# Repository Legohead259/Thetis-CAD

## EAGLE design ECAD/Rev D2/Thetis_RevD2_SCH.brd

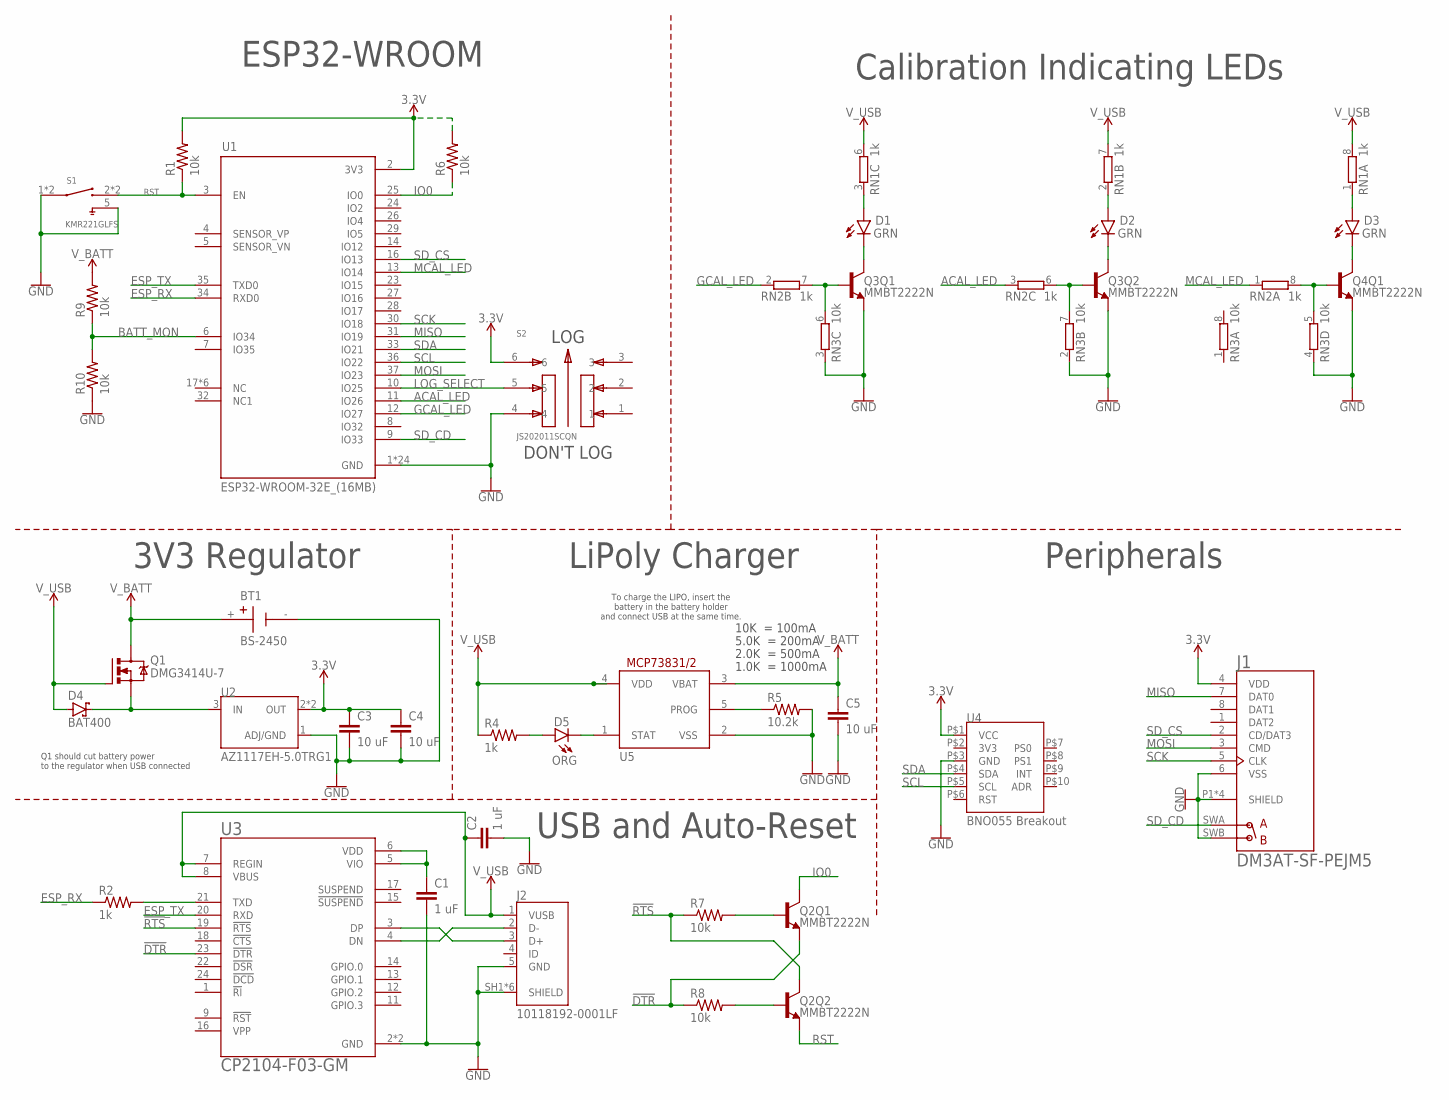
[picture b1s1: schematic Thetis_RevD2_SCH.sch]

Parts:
BT1: BS-2450; BAT_BS-2450
C1, C2: 1 uF; C0603
C3, C4, C5: 10 uF; C0603
D1, D2, D3: GRN; LEDC1608X65N
D4: BAT400; SOT23
D5: ORG; LEDC1608X65N
J1: DM3AT-SF-PEJM5; HRS_DM3AT-SF-PEJM5
J2: 10118192-0001LF; AMPHENOL_10118192-0001LF
Q1: DMG3414U-7; SOT23
Q2, Q3, Q4: MMBT2222N; SC70-6
R1, R6, R7, R8, R9, R10: 10k; R0603
R2, R4: 1k; R0603
R5: 10.2k; R0603
RN1, RN2: 1k; EXB28V
RN3: 10k; EXB28V
S1: KMR221GLFS; SW_KMR221GLFS
S2: JS202011SCQN; SW_JS202011SCQN
U1: ESP32-WROOM-32E_(16MB); MODULE_ESP32-WROOM-32E_(16MB)
U2: AZ1117EH-5.0TRG1; SOT230P700X180-4N
U3: CP2104-F03-GM; QFN50P400X400X80-25N
U4: BNO055 Breakout; ADAFRUIT-BNO055-BREAKOUT-SMD
U5: MCP73831/OT; SOT23-5L

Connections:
3.3V: C3.1, C4.1, J1.4 (VDD), R1.2, R6.2, S2.6, U1.2 (3V3), U2.2 (OUT), U2.4 (OUT), U4.P$1 (VCC)
3V3: U4.P$2 (3V3)
!DTR: Q2.4 (E), R8.1, U3.23 (!DTR)
!RTS: Q2.6 (C), R7.1, U3.19 (!RTS)
ACAL_LED: RN2.3 (1), U1.11 (IO26)
BATT_MON: R9.1, R10.2, U1.6 (IO34)
ESP_RX: R2.1, U1.34 (RXD0)
ESP_TX: U1.35 (TXD0), U3.20 (RXD)
GCAL_LED: RN2.2 (1), U1.12 (IO27)
GND: BT1.-, C1.2, C2.2, C3.2, C4.2, C5.2, J1.6 (VSS), J1.P1 (SHIELD), J1.P2 (SHIELD), J1.P3 (SHIELD), J1.P4 (SHIELD), J1.SWB (B), J2.5 (GND), J2.SH1 (SHIELD), J2.SH2 (SHIELD), J2.SH3 (SHIELD), J2.SH4 (SHIELD), J2.SH5 (SHIELD), J2.SH6 (SHIELD), Q3.1 (E), Q3.4 (E), Q4.4 (E), R5.2, R10.1, RN3.2 (1), RN3.3 (1), RN3.4 (1), S1.1, S1.4 (1), S1.5, S2.4, U1.1 (GND), U1.15 (GND), U1.38 (GND), U1.39_1 (GND), U1.39_2 (GND), U1.39_3 (GND), U1.39_4 (GND), U1.39_5 (GND), U1.39_6 (GND), U1.39_7 (GND), U1.39_8 (GND), U1.39_9 (GND), U1.39_10 (GND), U1.39_11 (GND), U1.39_12 (GND), U1.39_13 (GND), U1.39_14 (GND), U1.39_15 (GND), U1.39_16 (GND), U1.39_17 (GND), U1.39_18 (GND), U1.39_19 (GND), U1.39_20 (GND), U1.39_21 (GND), U2.1 (ADJ/GND), U3.2 (GND), U3.25 (GND), U4.P$3 (GND), U5.2 (VSS)
IO0: Q2.3 (C), R6.1, U1.25 (IO0)
LOG_SELECT: S2.5, U1.10 (IO25)
MCAL_LED: RN2.1, U1.13 (IO14)
MISO: J1.7 (DAT0), U1.31 (IO19)
MOSI: J1.3 (CMD), U1.37 (IO23)
unnamed: C1.1, U3.5 (VIO), U3.6 (VDD)
unnamed: R2.2, U3.21 (TXD)
unnamed: J2.3 (D+), U3.3 (DP)
unnamed: J2.2 (D-), U3.4 (DN)
unnamed: Q3.5 (B), RN2.7 (2), RN3.6 (2)
unnamed: Q2.2 (B), R8.2
unnamed: D1.C, Q3.3 (C)
unnamed: Q2.5 (B), R7.2
unnamed: D1.A, RN1.3 (1)
unnamed: D2.A, RN1.2 (1)
unnamed: D2.C, Q3.6 (C)
unnamed: D4.3 (C), Q1.2 (S), U2.3 (IN)
unnamed: Q3.2 (B), RN2.6 (2), RN3.7 (2)
unnamed: Q4.5 (B), RN2.8 (2), RN3.5 (2)
unnamed: D3.C, Q4.3 (C)
unnamed: D3.A, RN1.1
unnamed: D5.A, R4.2
unnamed: D5.C, U5.1 (STAT)
unnamed: R5.1, U5.5 (PROG)
RST: Q2.1 (E), R1.1, S1.2 (3), S1.3, U1.3 (EN)
SCK: J1.5 (CLK), U1.30 (IO18)
SCL: U1.36 (IO22), U4.P$5 (SCL)
SDA: U1.33 (IO21), U4.P$4 (SDA)
SD_CD: J1.SWA (A), U1.9 (IO33)
SD_CS: J1.2 (CD/DAT3), U1.16 (IO13)
V_BATT: BT1.+, C5.1, Q1.3 (D), R9.2, U5.3 (VBAT)
V_USB: C2.1, D4.1 (A), J2.1 (VUSB), Q1.1 (G), R4.1, RN1.6 (2), RN1.7 (2), RN1.8 (2), U3.7 (REGIN), U3.8 (VBUS), U5.4 (VDD)

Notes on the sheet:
LOG
DON'T LOG
10K = 100mA
5.0K = 200mA
2.0K = 500mA
1.0K = 1000mA
To charge the LIPO, insert the battery in the battery holder and connect USB at the same time.
LiPoly Charger
USB and Auto-Reset
3V3 Regulator
Q1 should cut battery power to the regulator when USB connected
Peripherals
Calibration Indicating LEDs
ESP32-WROOM

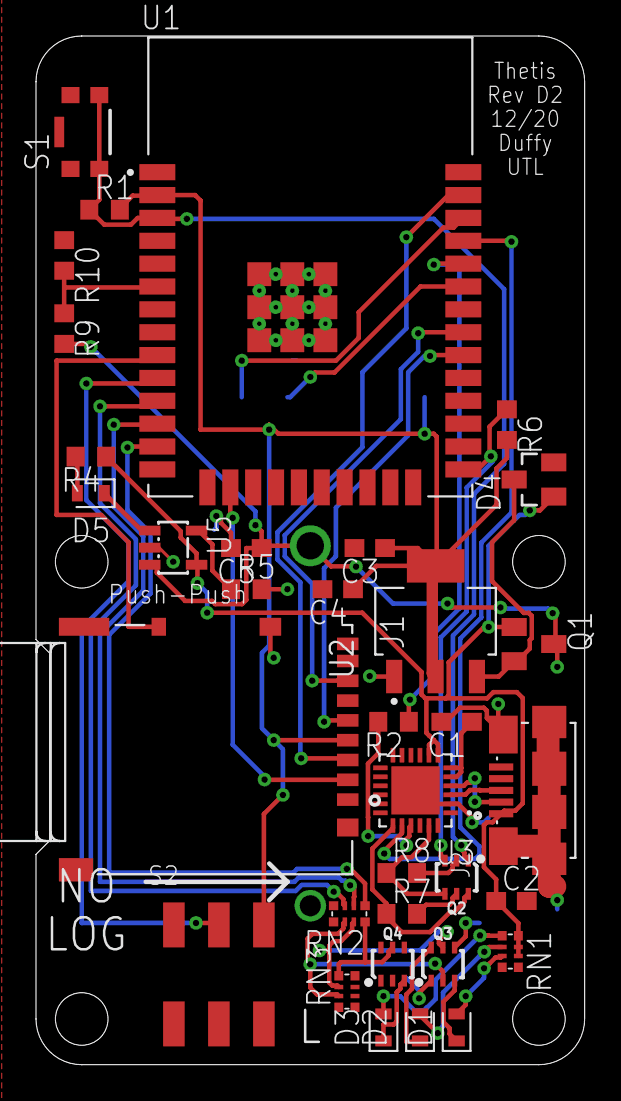
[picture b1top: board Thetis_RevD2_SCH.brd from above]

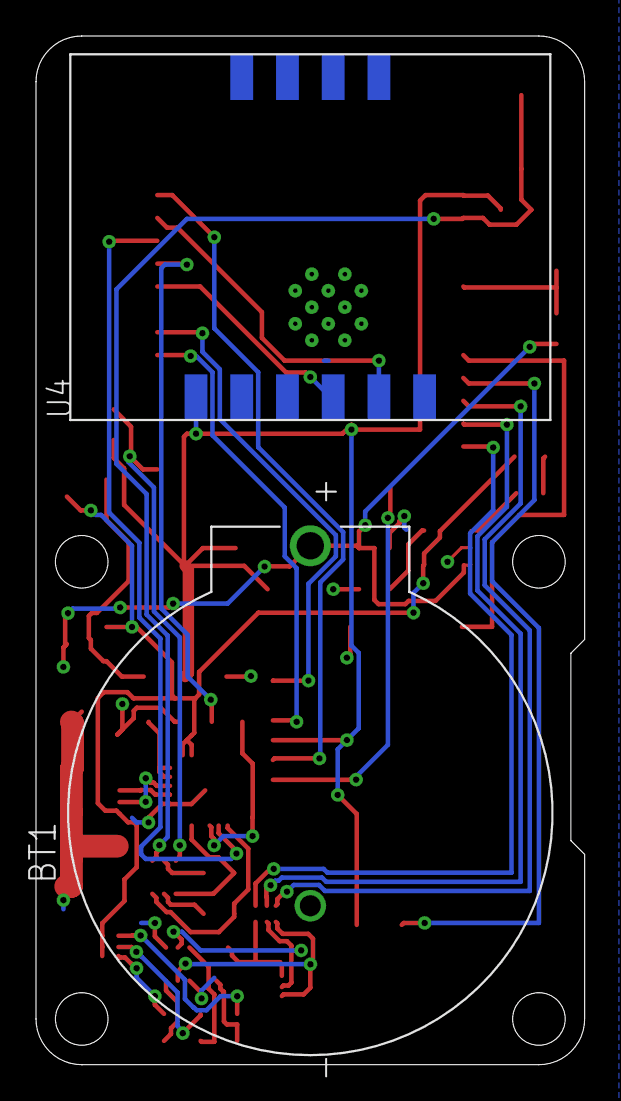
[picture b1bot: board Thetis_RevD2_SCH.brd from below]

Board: 2 copper layers, 30.5 x 57.1 mm, 36 parts (2 on the bottom side), 41 nets.

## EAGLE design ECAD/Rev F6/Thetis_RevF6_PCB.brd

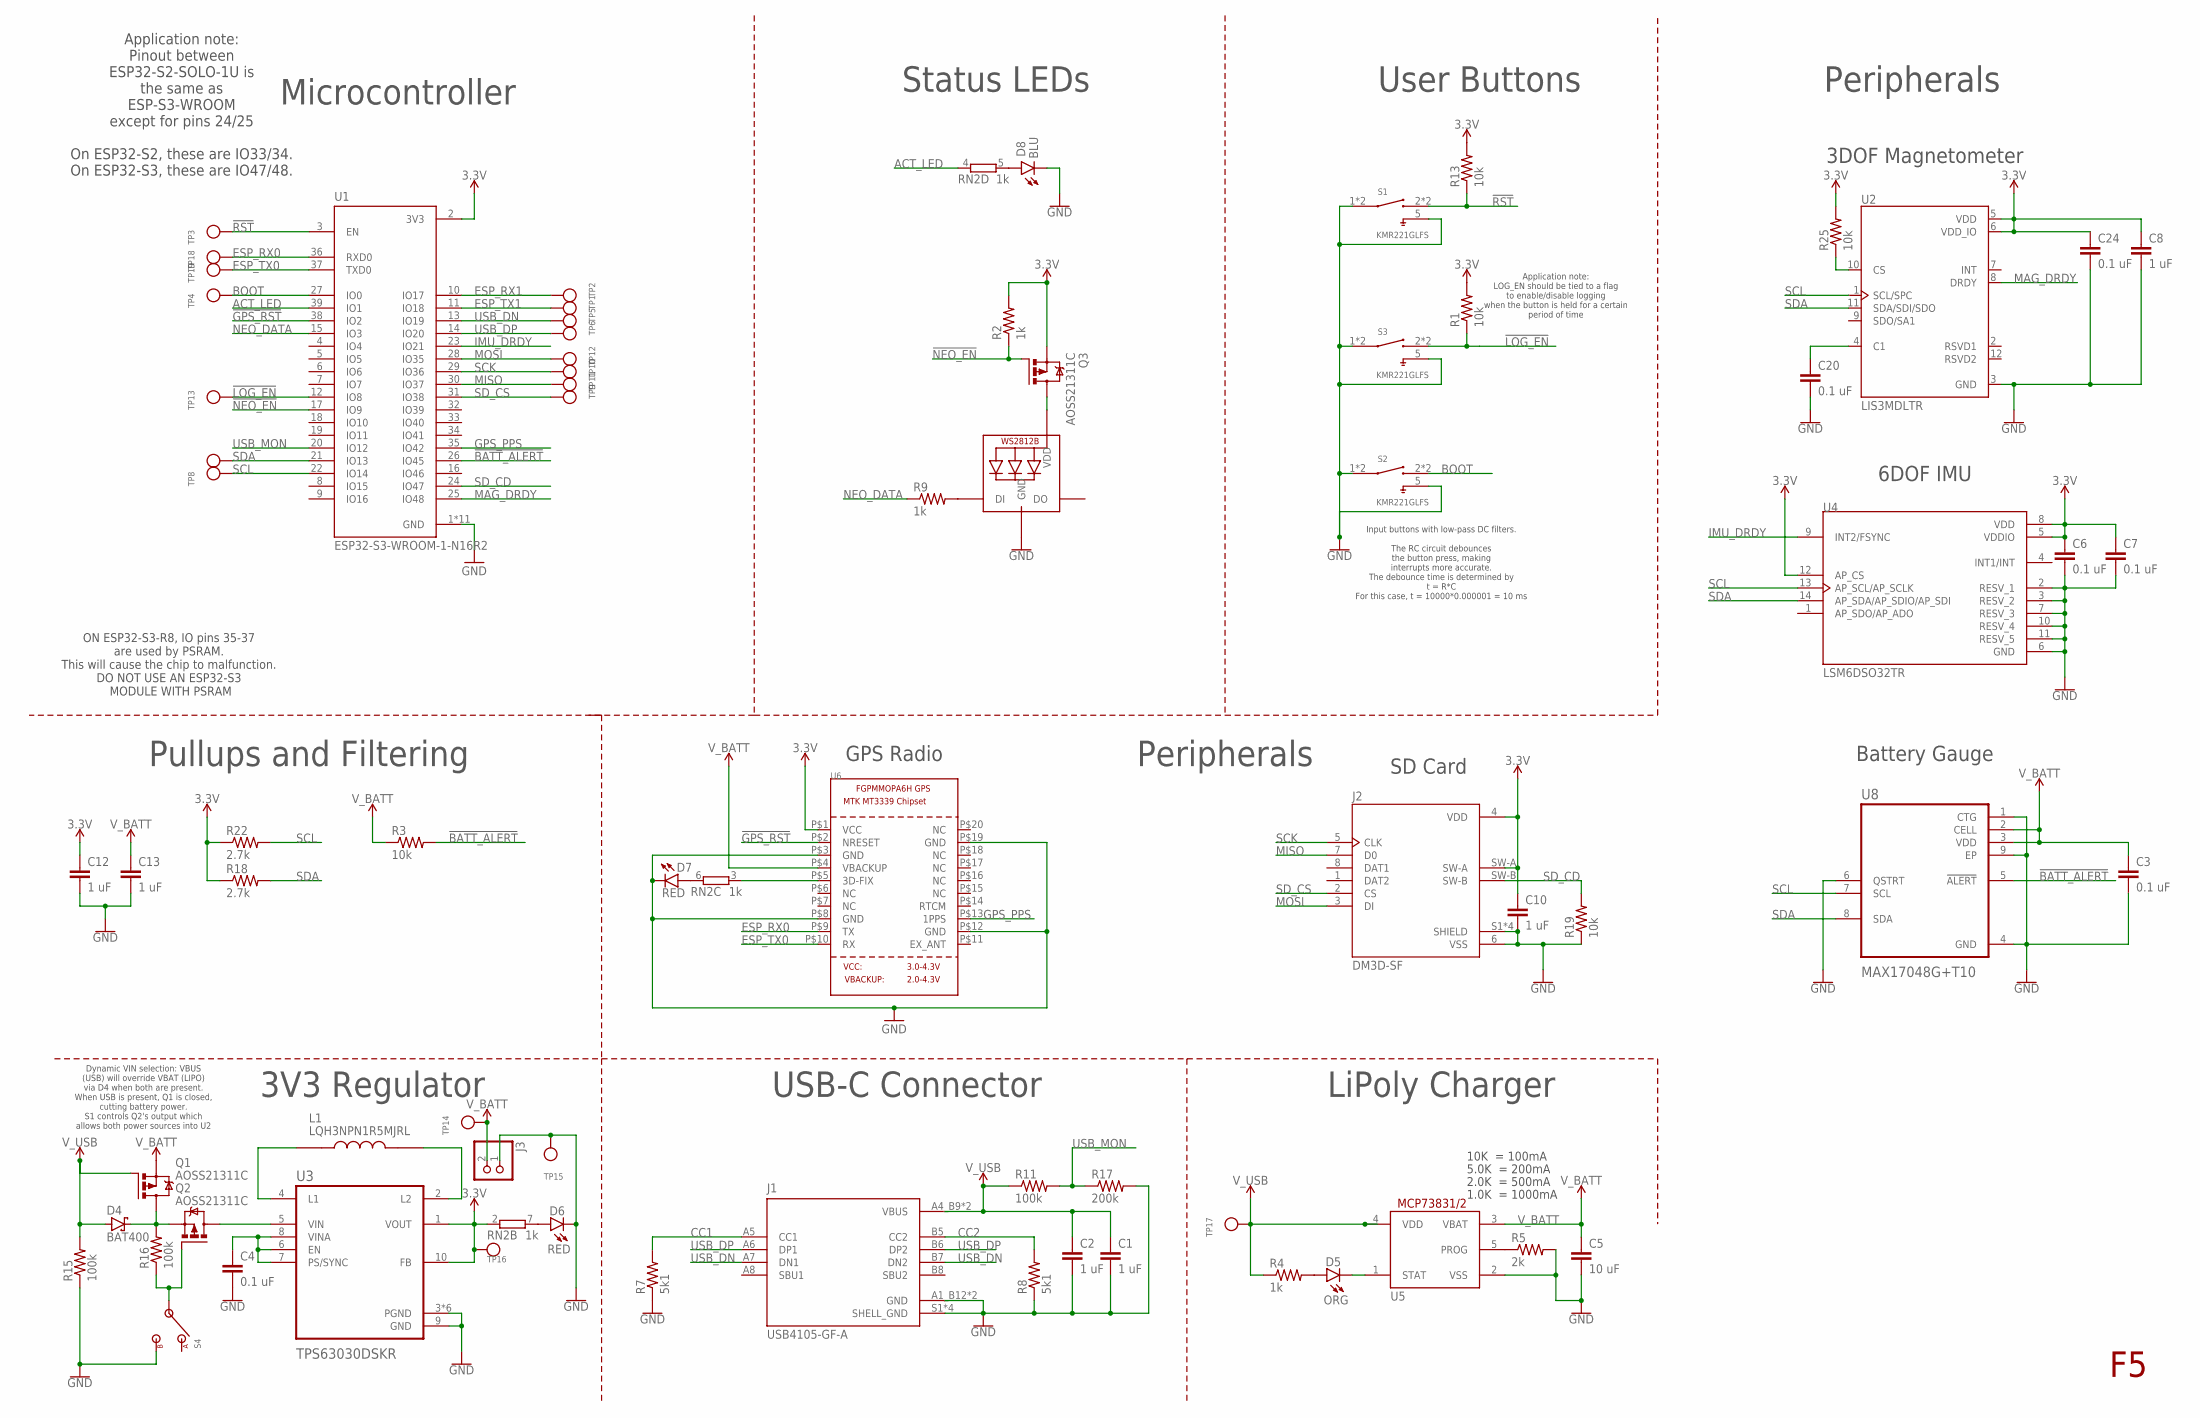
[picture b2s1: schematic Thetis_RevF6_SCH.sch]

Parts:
C1, C2, C8, C10, C12, C13: 1 uF; C0603
C3, C4, C6, C7, C20, C24: 0.1 uF; C0603
C5: 10 uF; C0603
D4: BAT400; SOT23
D5: ORG; LEDC1608X65N
D6: RED; LEDC1608X65N
D7: RED; LEDC1608X35N
D8: BLU; LEDC1608X65N
J1: USB4105-GF-A; GCT_USB4105-GF-A
J2: DM3D-SF; HRS_DM3D-SF
J3: JST_2PIN; JSTPH2
L1: LQH3NPN1R5MJRL; IND_LQH3NPN1R5MJRL
LED1: WS2812B3535; LED3535
Q1, Q2, Q3: AOSS21311C; SOT23
R1, R3, R13, R19, R25: 10k; R0603
R2, R4, R9: 1k; R0603
R5: 2k; R0603
R7, R8: 5k1; R0603
R11, R15, R16: 100k; R0603
R17: 200k; R0603
R18, R22: 2.7k; R0603
RN2: 1k; EXBN8V
S1, S2, S3: KMR221GLFS; SW_KMR221GLFS
S4: CL-SB-12X; CL-SB-12A
TP1, TP2, TP3, TP4, TP5, TP6, TP7, TP8, TP9, TP10, TP11, TP12, TP13, TP14, TP15, TP16, TP17, TP18, TP19: TESTPOINT1.5X2.0MM_NOCREAM; PAD-1.5X2.0
U1: ESP32-S3-WROOM-1-N16R2; XCVR_ESP32-S3-WROOM-1-N16R2
U2: LIS3MDLTR; XDCR_LIS3MDLTR
U3: TPS63030DSKR; SON50P250X250X80-11N
U4: LSM6DSO32TR; PQFN50P300X250X97-14N
U5: MCP73831/OT; SOT23-5L
U6: GPS_FGPMMOPA6H; FGPMMOPA6H
U8: MAX17048G+T10; SON50P200X200X80-9N

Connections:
3.3V: C6.1, C7.1, C8.1, C10.1, C12.1, C24.1, J2.4 (VDD), J2.SW-A, Q3.2 (S), R1.2, R2.2, R13.2, R18.1, R22.1, R25.2, RN2.2 (1), TP16.P$1, U1.2 (3V3), U2.5 (VDD), U2.6 (VDD_IO), U3.1 (VOUT), U3.10 (FB), U4.5 (VDDIO), U4.8 (VDD), U4.12 (AP_CS), U6.P$1 (VCC)
!BATT_ALERT: R3.2, U1.26 (IO45), U8.5 (!ALERT)
!GPS_RST: U1.38 (IO2), U6.P$2 (NRESET)
!LOG_EN: R1.1, S3.2 (3), S3.3, TP13.P$1, U1.12 (IO8)
!NEO_EN: Q3.1 (G), R2.1, U1.17 (IO9)
!RST: R13.1, S1.2 (3), S1.3, TP3.P$1, U1.3 (EN)
ACT_LED: RN2.4 (1), U1.39 (IO1)
BOOT: S2.2 (3), S2.3, TP4.P$1, U1.27 (IO0)
CC1: J1.A5 (CC1), R7.2
CC2: J1.B5 (CC2), R8.2
ESP_RX0: TP18.P$1, U1.36 (RXD0), U6.P$9 (TX)
ESP_RX1: TP2.P$1, U1.10 (IO17)
ESP_TX0: TP19.P$1, U1.37 (TXD0), U6.P$10 (RX)
ESP_TX1: TP1.P$1, U1.11 (IO18)
GND: C1.2, C2.2, C3.2, C4.2, C5.2, C6.2, C7.2, C8.2, C10.2, C12.2, C13.2, C20.2, C24.2, D6.C, D7.C, D8.C, J1.A1_B12 (GND), J1.B1_A12 (GND), J1.S1 (SHELL_GND), J1.S2 (SHELL_GND), J1.S3 (SHELL_GND), J1.S4 (SHELL_GND), J2.6 (VSS), J2.S1 (SHIELD), J2.S2 (SHIELD), J2.S3 (SHIELD), J2.S4 (SHIELD), J3.1, LED1.4 (GND), R5.2, R7.1, R8.1, R15.1, R17.2, R19.1, S1.1, S1.4 (1), S1.5, S2.1, S2.4 (1), S2.5, S3.1, S3.4 (1), S3.5, S4.3, TP15.P$1, U1.1 (GND), U1.40 (GND), U1.41_1 (GND), U1.41_2 (GND), U1.41_3 (GND), U1.41_4 (GND), U1.41_5 (GND), U1.41_6 (GND), U1.41_7 (GND), U1.41_8 (GND), U1.41_9 (GND), U2.3 (GND), U3.3 (PGND), U3.9 (GND), U3.11 (PGND), U3.12 (PGND), U3.13 (PGND), U3.14 (PGND), U3.15 (PGND), U4.2 (RESV_1), U4.3 (RESV_2), U4.6 (GND), U4.7 (RESV_3), U4.10 (RESV_4), U4.11 (RESV_5), U5.2 (VSS), U6.P$3 (GND), U6.P$8 (GND), U6.P$12 (GND), U6.P$19 (GND), U8.1 (CTG), U8.4 (GND), U8.6 (QSTRT), U8.9 (EP)
GPS_PPS: U1.35 (IO42), U6.P$13 (1PPS)
IMU_DRDY: U1.23 (IO21), U4.9 (INT2/FSYNC)
MAG_DRDY: U1.25 (IO48), U2.8 (DRDY)
MISO: J2.7 (D0), TP11.P$1, U1.30 (IO37)
MOSI: J2.3 (DI), TP12.P$1, U1.28 (IO35)
unnamed: Q2.1 (G), R16.1, S4.2
unnamed: D7.A, RN2.6 (2)
unnamed: D8.A, RN2.5 (2)
unnamed: Q2.3 (D), U3.5 (VIN)
unnamed: LED1.2 (VDD), Q3.3 (D)
unnamed: D6.A, RN2.7 (2)
unnamed: C20.1, U2.4 (C1)
unnamed: LED1.1 (DI), R9.2
unnamed: RN2.3 (1), U6.P$5 (3D-FIX)
unnamed: L1.1, U3.4 (L1)
unnamed: L1.2, U3.2 (L2)
unnamed: D4.3 (C), Q1.3 (D), Q2.2 (S), R16.2
unnamed: R25.1, U2.10 (CS)
unnamed: C4.1, U3.6 (EN), U3.7 (PS/SYNC), U3.8 (VINA)
unnamed: D5.A, R4.2
unnamed: D5.C, U5.1 (STAT)
unnamed: R5.1, U5.5 (PROG)
NEO_DATA: R9.1, U1.15 (IO3)
SCK: J2.5 (CLK), TP10.P$1, U1.29 (IO36)
SCL: R22.2, TP8.P$1, U1.22 (IO14), U2.1 (SCL/SPC), U4.13 (AP_SCL/AP_SCLK), U8.7 (SCL)
SDA: R18.2, TP7.P$1, U1.21 (IO13), U2.11 (SDA/SDI/SDO), U4.14 (AP_SDA/AP_SDIO/AP_SDI), U8.8 (SDA)
SD_CD: J2.SW-B, R19.2, U1.24 (IO47)
SD_CS: J2.2 (CS), TP9.P$1, U1.31 (IO38)
USB_DN: J1.A7 (DN1), J1.B7 (DN2), TP5.P$1, U1.13 (IO19)
USB_DP: J1.A6 (DP1), J1.B6 (DP2), TP6.P$1, U1.14 (IO20)
USB_MON: R11.2, R17.1, U1.20 (IO12)
V_BATT: C3.1, C5.1, C13.1, J3.2, Q1.2 (S), R3.1, TP14.P$1, U5.3 (VBAT), U6.P$4 (VBACKUP), U8.2 (CELL), U8.3 (VDD)
V_USB: C1.1, C2.1, D4.1 (A), J1.A4_B9 (VBUS), J1.B4_A9 (VBUS), Q1.1 (G), R4.1, R11.1, R15.2, TP17.P$1, U5.4 (VDD)

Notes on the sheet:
Peripherals
Status LEDs
Microcontroller
User Buttons
3DOF Magnetometer
6DOF IMU
Pullups and Filtering
Application note: Pinout between ESP32-S2-SOLO-1U is the same as ESP-S3-WROOM except for pins 24/25 On ESP32-S2, these are IO33/34. On ESP32-S3, these are IO47/48.
ON ESP32-S3-R8, IO pins 35-37 are used by PSRAM. This will cause the chip to malfunction. DO NOT USE AN ESP32-S3 MODULE WITH PSRAM
Input buttons with low-pass DC filters. The RC circuit debounces the button press, making interrupts more accurate. The debounce time is determined by t = R*C For this case, t = 10000*0.000001 = 10 ms
Application note: LOG_EN should be tied to a flag to enable/disable logging when the button is held for a certain period of time
GPS Radio
SD Card
10K = 100mA
5.0K = 200mA
2.0K = 500mA
1.0K = 1000mA
LiPoly Charger
3V3 Regulator
Dynamic VIN selection: VBUS (USB) will override VBAT (LIPO) via D4 when both are present. When USB is present, Q1 is closed, cutting battery power. S1 controls Q2's output which allows both power sources into U2
USB-C Connector
Battery Gauge

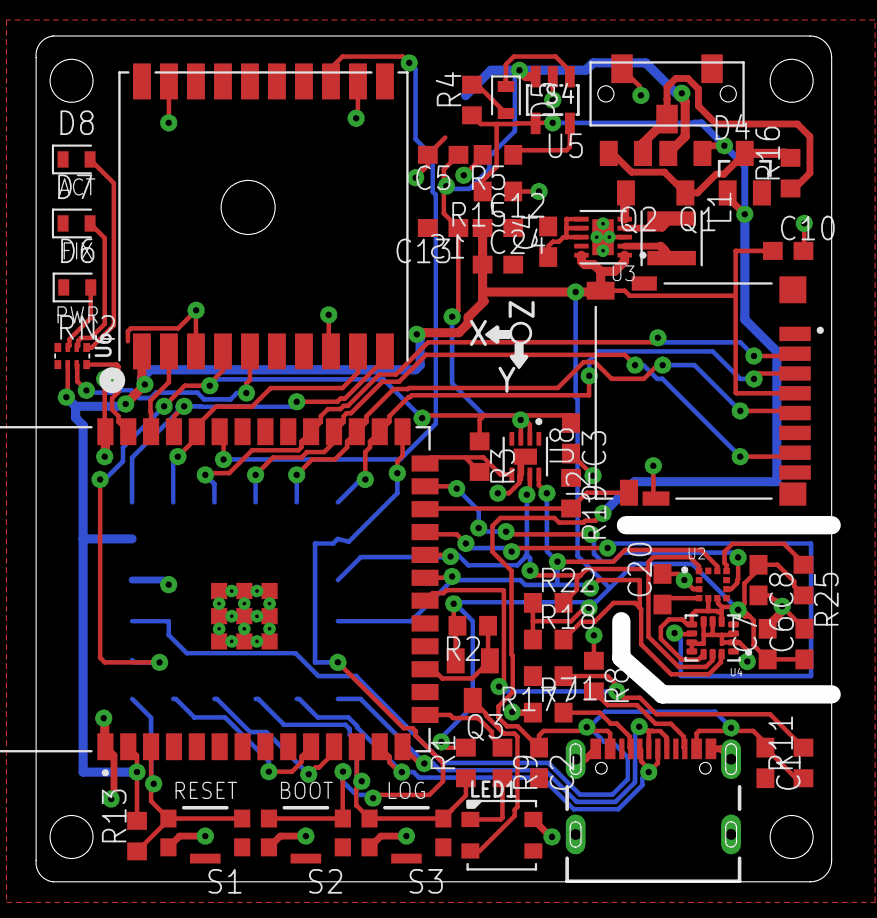
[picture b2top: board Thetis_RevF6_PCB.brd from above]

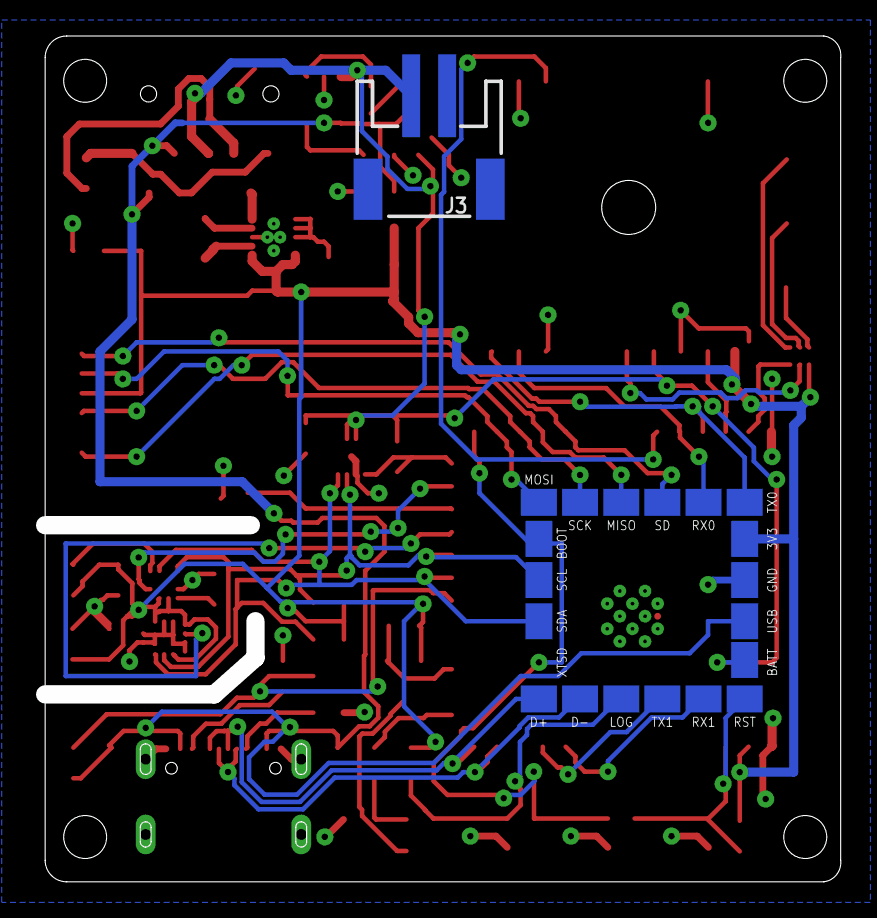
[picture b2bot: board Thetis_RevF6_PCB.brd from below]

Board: 2 copper layers, 44.2 x 47.0 mm, 74 parts (20 on the bottom side), 48 nets.

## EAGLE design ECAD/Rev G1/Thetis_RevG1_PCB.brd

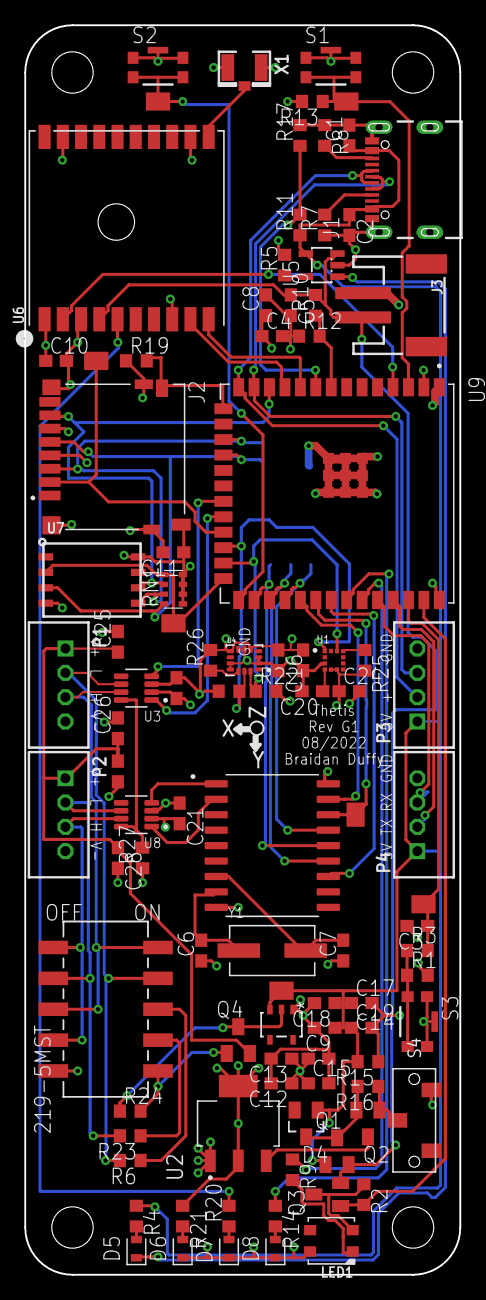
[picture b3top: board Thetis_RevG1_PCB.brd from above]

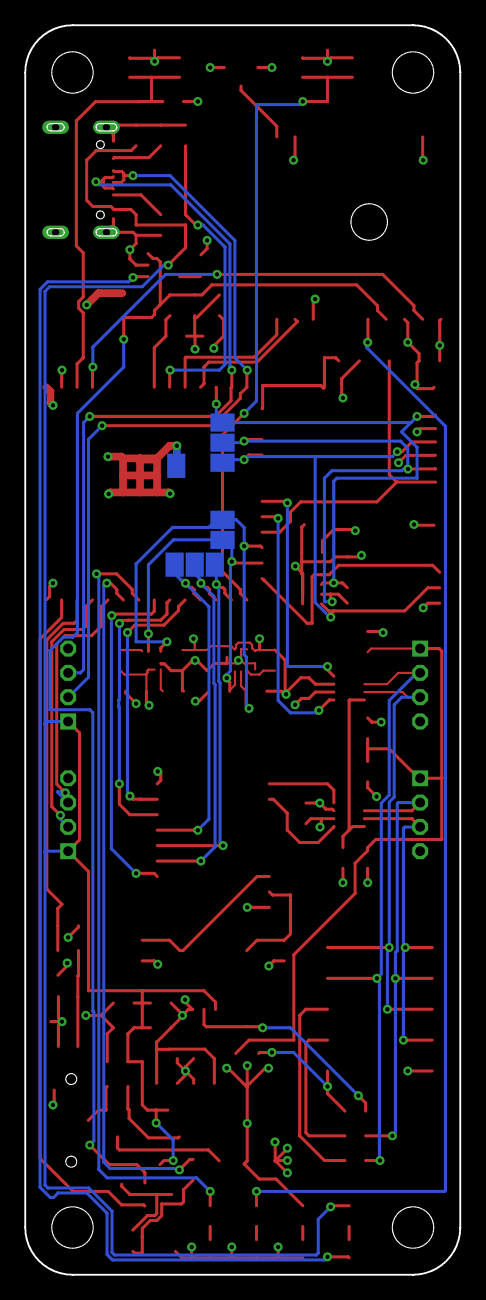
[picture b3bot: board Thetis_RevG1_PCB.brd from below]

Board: 4 copper layers, 35.8 x 102.8 mm, 107 parts (9 on the bottom side), 68 nets.

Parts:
C1, C2, C5: 10 uF; C0603
C3, C9, C10, C11, C12, C13, C14, C15, C17, C18, C19, C25, C26, C27, C28: 1 uF; C0603
C4, C8, C16, C20, C21, C22, C23, C24: 0.1 uF; C0603
C6, C7: 22 pF; C0603
D4: BAT400; SOT23
D5, D6, D8: LED_GREEN; LEDC1608X65N_RND-G
D7: LED_YELLOW; LEDC1608X35N_FLAT-Y
J1: USB4105-GF-A; GCT_USB4105-GF-A
J2: DM3D-SF; HRS_DM3D-SF
J3: 1S LiPo; JSTPH2
LED1: WS2812B3535; LED3535
P1: CAN0; B4B-PH-K
P2: CAN1; B4B-PH-K
P3: USB; B4B-PH-K
P4: UART; B4B-PH-K
Q1, Q2, Q3, Q4: AOSS21311C; SOT23
R1, R3, R13, R19, R25, R26, R27: 10k; R0603
R2, R11, R15, R16, R24: 100k; R0603
R4, R14, R20, R21: 1k; R0603
R5: 2k; R0603
R6, R23: 120; R0603
R7, R8: 5k1; R0603
R9: 480; R0603
R10, R12: 1M; R0603
R17: 200k; R0603
R18, R22: 2.7k; R0603
RN1: 10k; EXBV8V
S1, S2, S3: KMR221GLFS; SW_KMR221GLFS
S4: CL-SB-12X; CL-SB-12A
SW1: 219-5MST; SW5_219SMT
TP7, TP8, TP9, TP10, TP11, TP12, TP14, TP18, TP19, TP20, TP21, TP22, TP23, TP24, TP27, TP28: PAD-1.5X2.0
U1: LIS3MDLTR; XDCR_LIS3MDLTR
U2: AZ1117H-3.3TRE1; SOT230P700X180-4N
U3, U8: MAX3051EKA; SOT65P280X145-8N
U4: LSM6DSO32TR; PQFN50P300X250X97-14N
U5: MCP73831/OT; SOT23-5L
U6: FGPMMOPA6H
U7: LGA8_8X6
U9: ESP32-S2-SOLO-U-N4R2; XCVR_ESP32-S2-SOLO-U-N4R2
U10: AP7380; SOT_50WR-7_DIO-L
U11: MCP2515-I/SO; SOIC127P1030X265-18N
X1: U.FL
Y1: 16 MHz; XTAL_ECS-160-20-3X-TR

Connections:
3.3V: C4.1, C8.1, C10.1, C11.1, C12.1, C13.1, C14.1, C15.1, C16.1, C21.1, C22.1, C23.1, C24.1, J2.4, J2.SW-A, R1.2, R13.2, R18.2, R21.1, R22.2, R25.2, R26.2, RN1.1, RN1.2, RN1.3, RN1.4, U1.5, U1.6, U2.2, U2.4, U3.3, U4.5, U4.8, U6.P$1, U7.8, U8.3, U9.2, U11.18
!CAN_CS: TP21.P$1, U9.32, U11.16
!CAN_EN: R27.2, U3.8, U8.8
!CAN_INT: U9.33, U11.12
!CAN_RST: U9.31, U11.17
!EXT_PWR_EN: Q4.1, R24.2, SW1.6
!GPS_RST: U6.P$2, U9.4
!LOG_EN: C3.1, R3.2, TP28.P$1, U9.38
!NEO_EN: Q3.1, R2.2, U9.39
!RST: R13.1, S1.2, S1.3, TP20.P$1, U9.3
ACT_LED: R14.1, U9.34
BATT_MON: R10.1, R12.2, U9.8
BOOT: S2.2, S2.3, TP19.P$1, U9.27
CAN0_H: P1.3, SW1.3, SW1.10, U3.7
CAN0_L: P1.2, R6.2, SW1.9, U3.6
CAN0_RXD: U3.1, U9.22
CAN0_TXD: U3.4, U9.21
CAN1_H: P2.3, SW1.1, SW1.4, U8.7
CAN1_L: P2.2, R23.2, SW1.2, U8.6
CAN1_RXD: U8.1, U11.2
CAN1_TXD: U8.4, U11.1
CAN_MISO: TP22.P$1, U9.30, U11.15
CAN_MOSI: TP23.P$1, U9.28, U11.14
CAN_SCK: TP24.P$1, U9.29, U11.13
CC1: J1.A5, R7.2
CC2: J1.B5, R8.2
ESP_RX0: P4.3, U9.36
ESP_RX1: U6.P$9, U9.11
ESP_TX0: P4.2, U9.37
ESP_TX1: U6.P$10, U9.10
GND: C1.2, C2.2, C3.2, C4.2, C5.2, C6.1, C7.1, C8.2, C9.2, C10.2, C11.2, C12.2, C13.2, C14.2, C15.2, C16.2, C17.2, C18.2, C19.2, C20.2, C21.2, C22.2, C23.2, C24.2, C25.2, C26.2, C27.2, C28.2, D6.C, D7.C, D8.C, J1.A1_B12, J1.B1_A12, J1.S1, J1.S2, J1.S3, J1.S4, J2.6, J2.S1, J2.S2, J2.S3, J2.S4, J3.1, LED1.4, P1.4, P2.4, P3.4, P4.4, R5.2, R7.1, R8.1, R12.1, R15.1, R17.2, R19.1, R27.1, S1.1, S1.4, S1.5, S2.1, S2.4, S2.5, S3.1, S3.4, S3.5, S4.3, SW1.5, TP14.P$1, U1.3, U2.1, U3.2, U4.2, U4.3, U4.6, U4.7, U4.10, U4.11, U5.2, U6.P$3, U6.P$8, U6.P$12, U6.P$19, U7.4, U8.2, U9.1, U9.40, U9.41_1, U9.41_2, U9.41_3, U9.41_4, U9.41_5, U9.41_6, U9.41_7, U9.41_8, U9.41_9, U10.1, U11.9, X1.1, X1.2
GPS_FIX: R20.2, U6.P$5
MISO: J2.7, RN1.6, TP11.P$1, U7.6, U9.12
MOSI: J2.3, RN1.7, TP9.P$1, U7.5, U9.17
unnamed: Q2.1, R16.1, S4.2
unnamed: D7.A, R20.1
unnamed: D8.A, R14.2
unnamed: R1.1, R3.1, S3.2, S3.3
unnamed: LED1.2, Q3.3, R2.1
unnamed: Q2.3, U2.3
unnamed: C20.1, U1.4
unnamed: LED1.1, R9.2
unnamed: U6.P$11, X1.3
unnamed: R6.1, SW1.8
unnamed: R26.1, U4.12
unnamed: D4.3, Q1.3, Q2.2, R16.2
unnamed: R23.1, SW1.7
unnamed: R25.1, U1.10
unnamed: Q4.3, R24.1, U10.2
unnamed: D5.A, R4.2
unnamed: D5.C, U5.1
unnamed: R5.1, U5.5
unnamed: D6.A, R21.2
NEO_DATA: R9.1, U9.35
OSC1: C6.2, U11.8, Y1.1
OSC2: C7.2, U11.7, Y1.2
SCK: J2.5, RN1.8, TP10.P$1, U7.3, U9.18
SCL: R18.1, TP8.P$1, U1.1, U4.13, U9.24
SDA: R22.1, TP7.P$1, U1.11, U4.14, U9.25
SD_CD: J2.SW-B, R19.2, U9.15
SD_CS: J2.2, TP12.P$1, U9.23
USB_DN: J1.A7, J1.B7, P3.3, U9.13
USB_DP: J1.A6, J1.B6, P3.2, U9.14
USB_MON: R11.2, R17.1, U9.9
VIN: C25.1, C26.1, C27.1, C28.1, P1.1, P2.1, Q4.2
V_BATT: C5.1, J3.2, Q1.2, Q3.2, R10.2, U5.3, U6.P$4
V_USB: C1.1, C2.1, C9.1, C17.1, C18.1, C19.1, D4.1, J1.A4_B9, J1.B4_A9, P3.1, P4.1, Q1.1, R4.1, R11.1, R15.2, TP27.P$1, U5.4, U10.3
XTSD_CS: RN1.5, TP18.P$1, U7.2, U9.26

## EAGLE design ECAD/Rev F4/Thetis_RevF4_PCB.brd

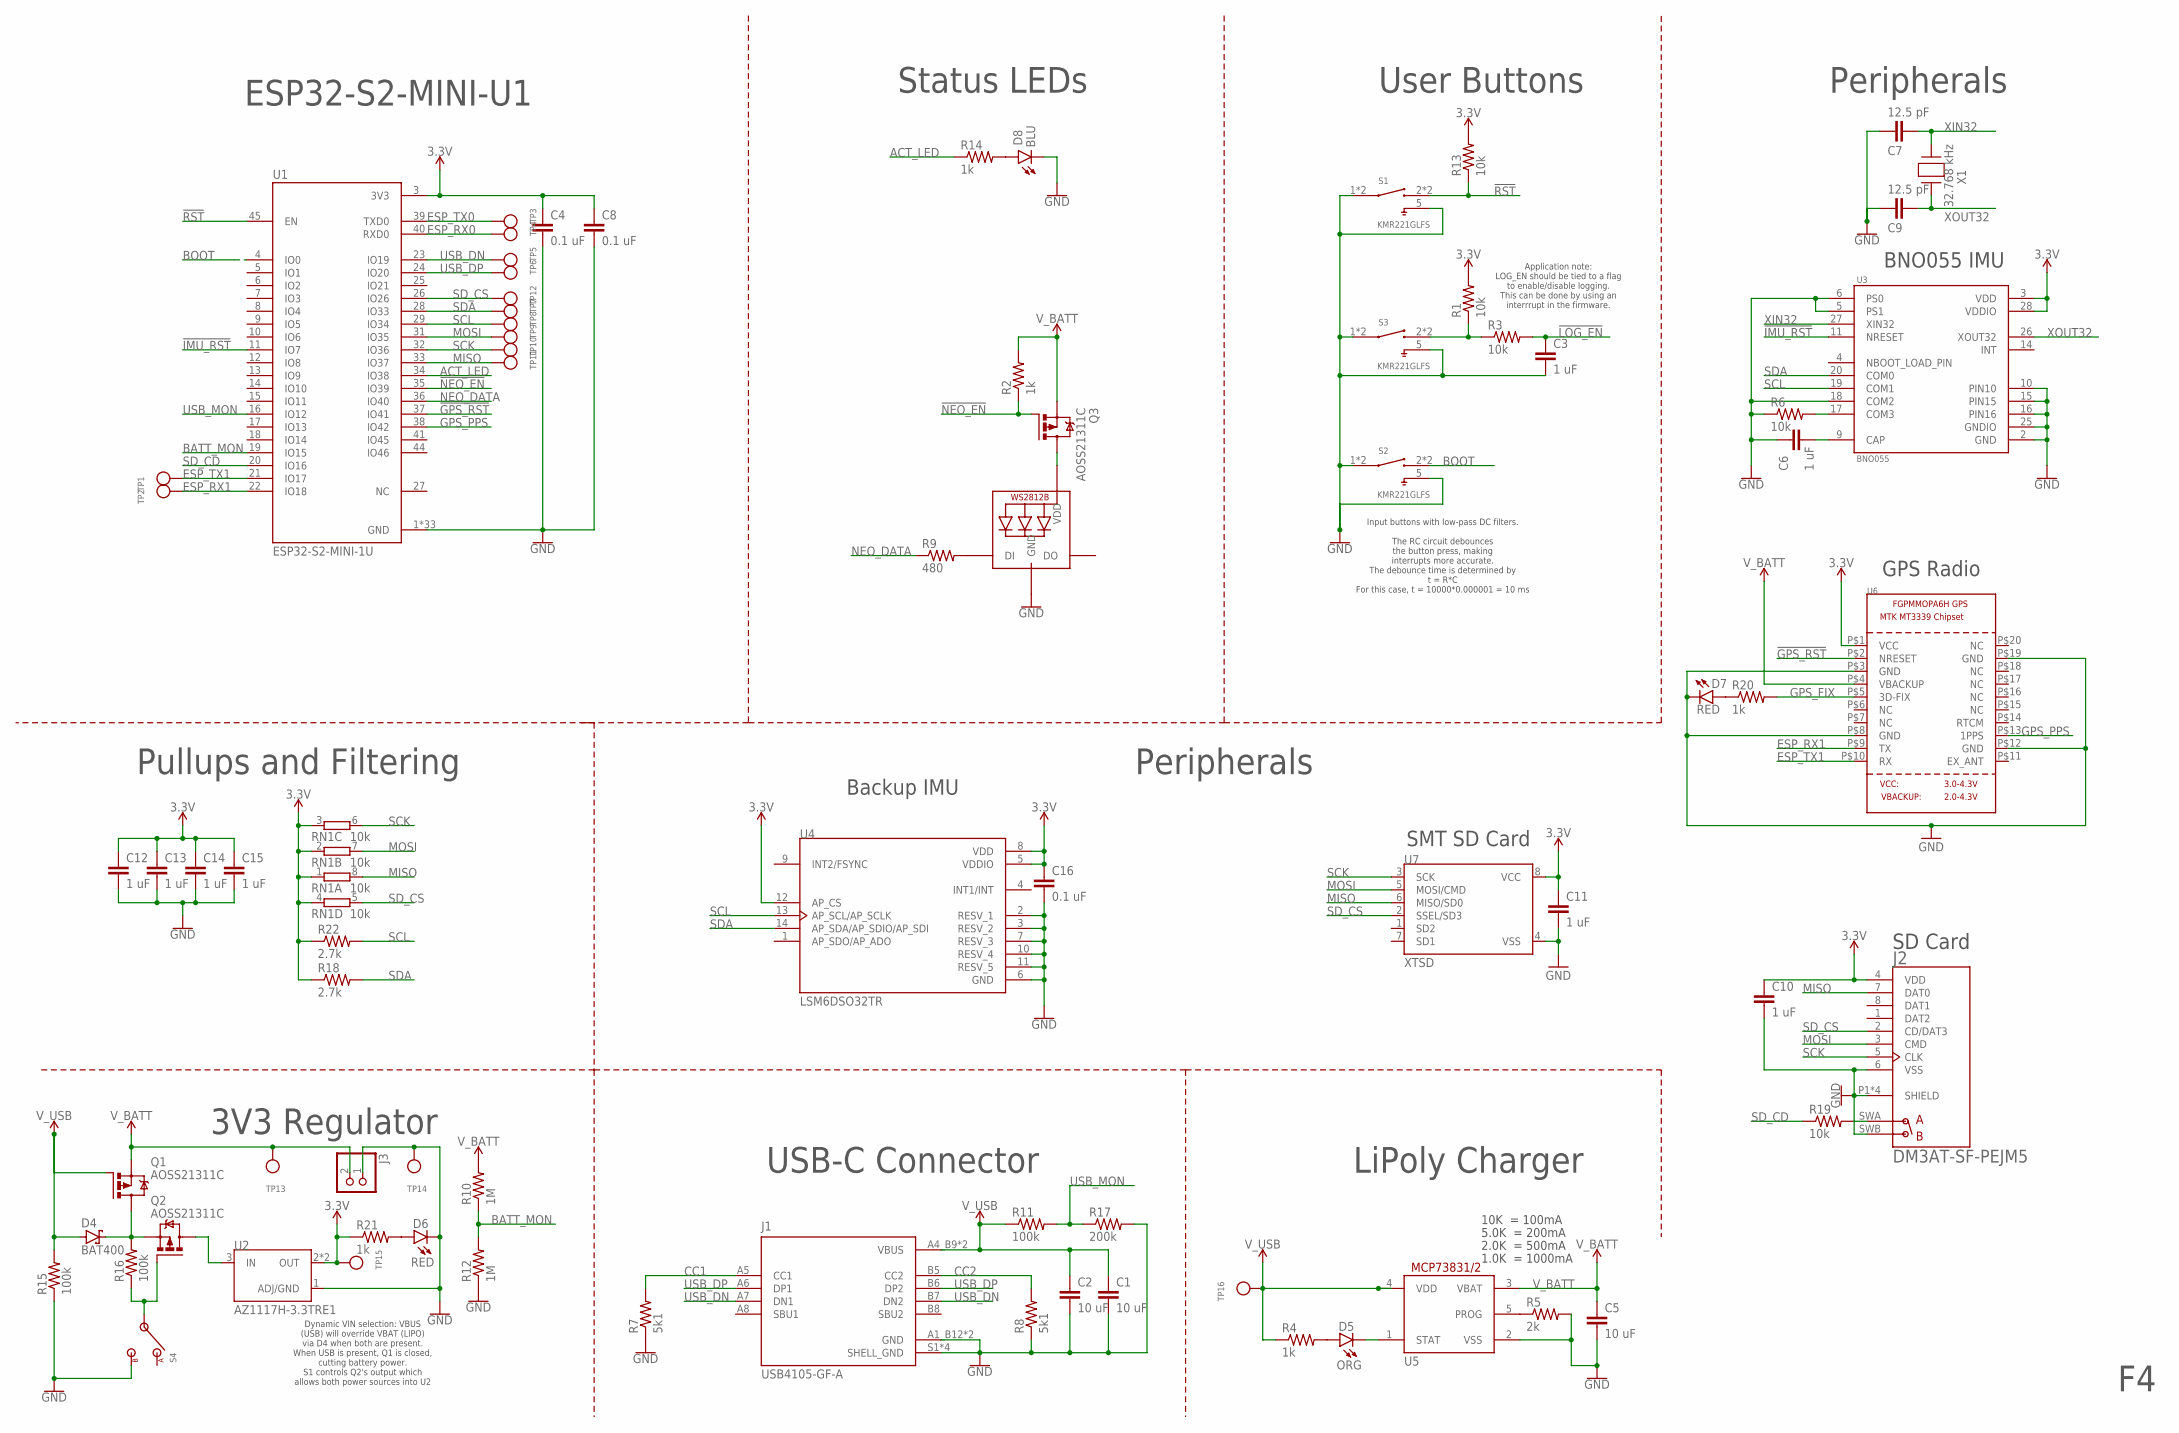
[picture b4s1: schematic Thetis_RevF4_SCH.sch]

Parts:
C1, C2, C5: 10 uF; C0603
C3, C6, C10, C11, C12, C13, C14, C15: 1 uF; C0603
C4, C8, C16: 0.1 uF; C0603
C7, C9: 12.5 pF; C0603
D4: BAT400; SOT23
D5: ORG; LEDC1608X65N
D6: RED; LEDC1608X65N
D7: RED; LEDC1608X35N
D8: BLU; LEDC1608X65N
J1: USB4105-GF-A; GCT_USB4105-GF-A
J2: DM3AT-SF-PEJM5; HRS_DM3AT-SF-PEJM5
J3: JST_2PIN; JSTPH2
LED1: WS2812B3535; LED3535
Q1, Q2, Q3: AOSS21311C; SOT23
R1, R3, R6, R13, R19: 10k; R0603
R2, R4, R14, R20, R21: 1k; R0603
R5: 2k; R0603
R7, R8: 5k1; R0603
R9: 480; R0603
R10, R12: 1M; R0603
R11, R15, R16: 100k; R0603
R17: 200k; R0603
R18, R22: 2.7k; R0603
RN1: 10k; EXBN8V
S1, S2, S3: KMR221GLFS; SW_KMR221GLFS
S4: CL-SB-12X; CL-SB-12A
TP1, TP2, TP3, TP4, TP5, TP6, TP7, TP8, TP9, TP10, TP11, TP12, TP13, TP14, TP15, TP16: TESTPOINT1.5X2.0MM_NOCREAM; PAD-1.5X2.0
U1: ESP32-S2-MINI-1U; XCVR_ESP32-S2-MINI-1U
U2: AZ1117H-3.3TRE1; SOT230P700X180-4N
U3: BNO055; LGA28R50P4X10_380X520X100
U4: LSM6DSO32TR; PQFN50P300X250X97-14N
U5: MCP73831/OT; SOT23-5L
U6: GPS_FGPMMOPA6H; FGPMMOPA6H
U7: XTSD; LGA8_8X6
X1: 32.768 kHz; RT3215_RAL-L

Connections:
3.3V: C4.1, C8.1, C10.1, C11.1, C12.1, C13.1, C14.1, C15.1, C16.1, J2.4 (VDD), R1.2, R13.2, R18.1, R21.1, R22.1, RN1.1, RN1.2 (1), RN1.3 (1), RN1.4 (1), TP15.P$1, U1.3 (3V3), U2.2 (OUT), U2.4 (OUT), U3.3 (VDD), U3.28 (VDDIO), U4.5 (VDDIO), U4.8 (VDD), U4.12 (AP_CS), U6.P$1 (VCC), U7.8 (VCC)
!GPS_RST: U1.37 (IO41), U6.P$2 (NRESET)
!IMU_RST: U1.11 (IO7), U3.11 (NRESET)
!LOG_EN: C3.1, R3.2
!NEO_EN: Q3.1 (G), R2.1, U1.35 (IO39)
!RST: R13.1, S1.2 (3), S1.3, U1.45 (EN)
ACT_LED: R14.1, U1.34 (IO38)
BATT_MON: R10.1, R12.2, U1.19 (IO15)
BOOT: S2.2 (3), S2.3, U1.4 (IO0)
CC1: J1.A5 (CC1), R7.2
CC2: J1.B5 (CC2), R8.2
ESP_RX0: TP4.P$1, U1.40 (RXD0)
ESP_RX1: TP2.P$1, U1.22 (IO18), U6.P$9 (TX)
ESP_TX0: TP3.P$1, U1.39 (TXD0)
ESP_TX1: TP1.P$1, U1.21 (IO17), U6.P$10 (RX)
GND: C1.2, C2.2, C3.2, C4.2, C5.2, C6.1, C7.1, C8.2, C9.1, C10.2, C11.2, C12.2, C13.2, C14.2, C15.2, C16.2, D6.C, D7.C, D8.C, J1.A1_B12 (GND), J1.B1_A12 (GND), J1.S1 (SHELL_GND), J1.S2 (SHELL_GND), J1.S3 (SHELL_GND), J1.S4 (SHELL_GND), J2.6 (VSS), J2.P1 (SHIELD), J2.P2 (SHIELD), J2.P3 (SHIELD), J2.P4 (SHIELD), J2.SWB (B), J3.1, LED1.4 (GND), R5.2, R6.1, R7.1, R8.1, R12.1, R15.1, R17.2, S1.1, S1.4 (1), S1.5, S2.1, S2.4 (1), S2.5, S3.1, S3.4 (1), S3.5, S4.3, TP14.P$1, U1.1 (GND), U1.2 (GND), U1.30 (GND), U1.42 (GND), U1.43 (GND), U1.46 (GND), U1.47 (GND), U1.48 (GND), U1.49 (GND), U1.50 (GND), U1.51 (GND), U1.52 (GND), U1.53 (GND), U1.54 (GND), U1.55 (GND), U1.56 (GND), U1.57 (GND), U1.58 (GND), U1.59 (GND), U1.60 (GND), U1.61_0 (GND), U1.61_1 (GND), U1.61_2 (GND), U1.61_3 (GND), U1.61_4 (GND), U1.61_5 (GND), U1.61_6 (GND), U1.61_7 (GND), U1.61_8 (GND), U1.62 (GND), U1.63 (GND), U1.64 (GND), U1.65 (GND), U2.1 (ADJ/GND), U3.2 (GND), U3.5 (PS1), U3.6 (PS0), U3.10 (PIN10), U3.15 (PIN15), U3.16 (PIN16), U3.18 (COM2), U3.25 (GNDIO), U4.2 (RESV_1), U4.3 (RESV_2), U4.6 (GND), U4.7 (RESV_3), U4.10 (RESV_4), U4.11 (RESV_5), U5.2 (VSS), U6.P$3 (GND), U6.P$8 (GND), U6.P$12 (GND), U6.P$19 (GND), U7.4 (VSS)
GPS_FIX: R20.2, U6.P$5 (3D-FIX)
GPS_PPS: U1.38 (IO42), U6.P$13 (1PPS)
MISO: J2.7 (DAT0), RN1.8 (2), TP11.P$1, U1.33 (IO37), U7.6 (MISO/SD0)
MOSI: J2.3 (CMD), RN1.7 (2), TP9.P$1, U1.31 (IO35), U7.5 (MOSI/CMD)
unnamed: Q2.1 (G), R16.1, S4.2
unnamed: D7.A, R20.1
unnamed: D8.A, R14.2
unnamed: R1.1, R3.1, S3.2 (3), S3.3
unnamed: LED1.2 (VDD), Q3.3 (D)
unnamed: Q2.3 (D), U2.3 (IN)
unnamed: R6.2, U3.17 (COM3)
unnamed: LED1.1 (DI), R9.2
unnamed: C6.2, U3.9 (CAP)
unnamed: D4.3 (C), Q1.3 (D), Q2.2 (S), R16.2
unnamed: D5.A, R4.2
unnamed: D5.C, U5.1 (STAT)
unnamed: R5.1, U5.5 (PROG)
unnamed: J2.SWA (A), R19.2
unnamed: D6.A, R21.2
NEO_DATA: R9.1, U1.36 (IO40)
SCK: J2.5 (CLK), RN1.6 (2), TP10.P$1, U1.32 (IO36), U7.3 (SCK)
SCL: R22.2, TP8.P$1, U1.29 (IO34), U3.19 (COM1), U4.13 (AP_SCL/AP_SCLK)
SDA: R18.2, TP7.P$1, U1.28 (IO33), U3.20 (COM0), U4.14 (AP_SDA/AP_SDIO/AP_SDI)
SD_CD: R19.1, U1.20 (IO16)
SD_CS: J2.2 (CD/DAT3), RN1.5 (2), TP12.P$1, U1.26 (IO26), U7.2 (SSEL/SD3)
USB_DN: J1.A7 (DN1), J1.B7 (DN2), TP5.P$1, U1.23 (IO19)
USB_DP: J1.A6 (DP1), J1.B6 (DP2), TP6.P$1, U1.24 (IO20)
USB_MON: R11.2, R17.1, U1.16 (IO12)
V_BATT: C5.1, J3.2, Q1.2 (S), Q3.2 (S), R2.2, R10.2, TP13.P$1, U5.3 (VBAT), U6.P$4 (VBACKUP)
V_USB: C1.1, C2.1, D4.1 (A), J1.A4_B9 (VBUS), J1.B4_A9 (VBUS), Q1.1 (G), R4.1, R11.1, R15.2, TP16.P$1, U5.4 (VDD)
XIN32: C7.2, U3.27 (XIN32), X1.1
XOUT32: C9.2, U3.26 (XOUT32), X1.2

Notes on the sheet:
10K = 100mA
5.0K = 200mA
2.0K = 500mA
1.0K = 1000mA
LiPoly Charger
3V3 Regulator
Peripherals
Status LEDs
ESP32-S2-MINI-U1
GPS Radio
Dynamic VIN selection: VBUS (USB) will override VBAT (LIPO) via D4 when both are present. When USB is present, Q1 is closed, cutting battery power. S1 controls Q2's output which allows both power sources into U2
USB-C Connector
Input buttons with low-pass DC filters. The RC circuit debounces the button press, making interrupts more accurate. The debounce time is determined by t = R*C For this case, t = 10000*0.000001 = 10 ms
User Buttons
Application note: LOG_EN should be tied to a flag to enable/disable logging. This can be done by using an interrrupt in the firmware.
BNO055 IMU
SD Card
SMT SD Card
Backup IMU
Pullups and Filtering

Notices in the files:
parts and their libraries:
SparkFun-DiscreteSemi-Poseidon-Edit: Licensing: Creative Commons ShareAlike 4.0 International - https://creativecommons.org/licenses/by-sa/4.0
microbuilder: This work is placed in the public domain, and may be freely used for commercial and non-commercial work with the following conditions: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
